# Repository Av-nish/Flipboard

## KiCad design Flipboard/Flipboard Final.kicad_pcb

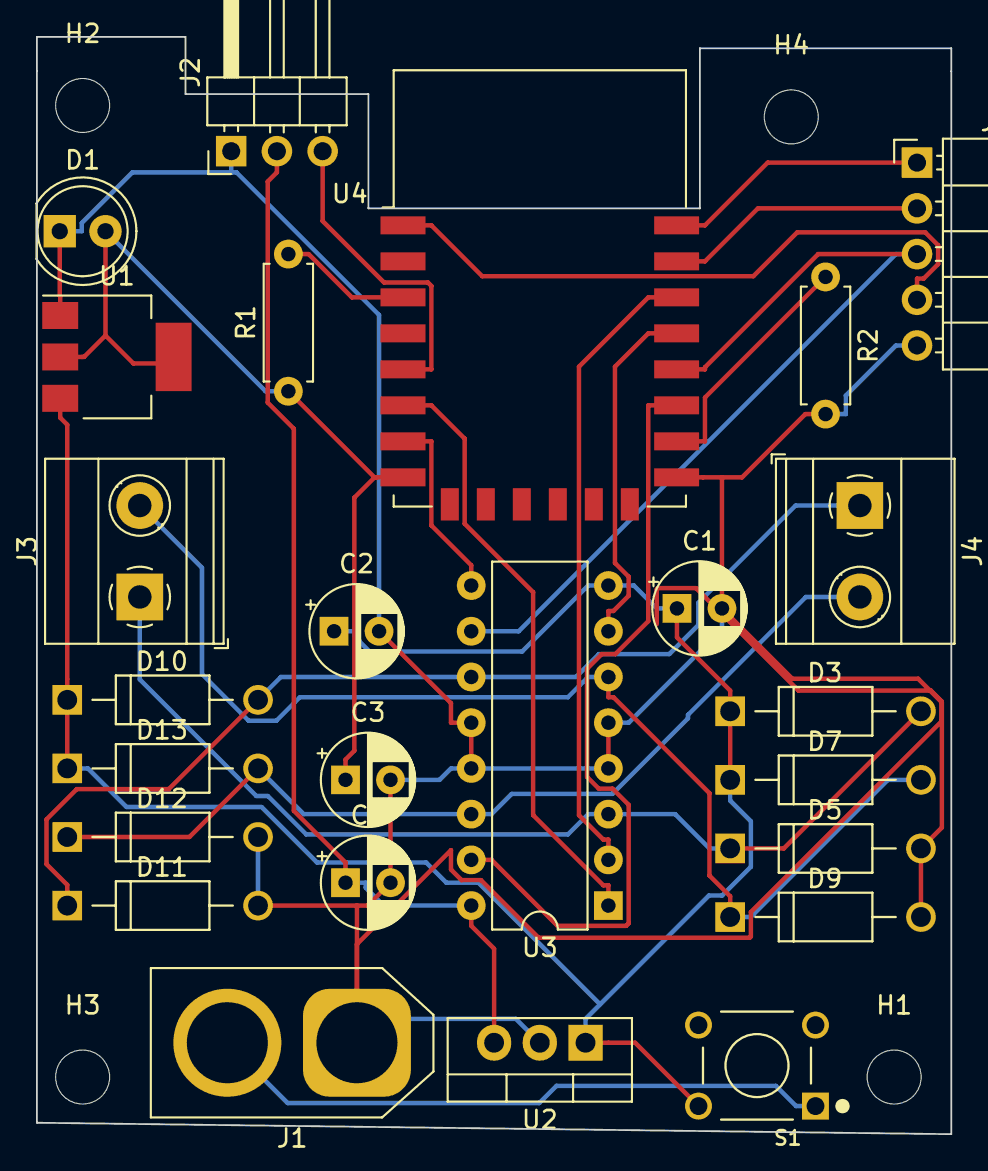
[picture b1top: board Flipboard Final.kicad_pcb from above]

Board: 2 copper layers, 50.8 x 61.0 mm, 29 parts (0 on the bottom side), 21 nets.

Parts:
C1, C2, C3, C4: CP; CP_Radial_D5.0mm_P2.50mm
D1: LED; LED_D5.0mm_Clear
D3, D5, D7, D9, D10, D11, D12, D13: 1N4007; DIOAD1060W80L520D270
H1, H2, H3, H4: MountingHole; MountingHole_3mm
J1: XT60-M-XT60-M; AMASS_XT60-M_1x02_P7.20mm_Vertical
J2: Conn_01x03; PinHeader_1x03_P2.54mm_Horizontal
J3, J4: Screw_Terminal_01x02; TerminalBlock_Phoenix_MKDS-1,5-2-5.08_1x02_P5.08mm_Horizont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
J5: Conn_01x05; PinHeader_1x05_P2.54mm_Horizontal
R1, R2: R; R_Axial_DIN0207_L6.3mm_D2.5mm_P7.62mm_Horizontal
S1: FSM8JH; SW_FSM8JH
U1: AMS1117-3.3; SOT-223-3_TabPin2
U2: L7805; TO-220-3_Vertical
U3: L293D; DIP-16_W7.62mm
U4: ESP-12F; ESP-12E

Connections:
unnamed: C1.1, C2.1, D3.C, D7.C, D10.C, D13.C, S1.3, U1.3, U2.1, U3.8
unnamed: C1.2, C2.2, C3.2, C4.2, D1.1, D5.A, D9.A, D11.A, D12.A, J1.1, J2.1, J5.5, R2.2, U1.1, U2.2, U3.4, U3.5, U3.12, U3.13, U4.15
unnamed: C3.1, D1.2, R1.1, U1.2, U4.8
unnamed: C4.1, J2.2, U2.3, U3.16
unnamed: D3.A, D5.C, J3.1, U3.3
unnamed: D7.A, D9.C, J3.2, U3.6
unnamed: D10.A, D11.C, J4.1, U3.11
unnamed: D12.C, D13.A, J4.2, U3.14
unnamed: J1.2, S1.1
unnamed: J2.3, U4.5
unnamed: J5.1, U4.22
unnamed: J5.2, U4.21
unnamed: J5.3, U3.10, U4.18
unnamed: J5.4, U4.1
unnamed: R1.2, U4.3
unnamed: R2.1, U4.16
unnamed: U3.1, U4.6
unnamed: U3.2, U4.20
unnamed: U3.7, U4.19
unnamed: U3.9, U4.7
unnamed: U3.15, U4.17

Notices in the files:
Flipboard/Flipboard Final.kicad_pcb:
Copyright (C) 2021 Bot
